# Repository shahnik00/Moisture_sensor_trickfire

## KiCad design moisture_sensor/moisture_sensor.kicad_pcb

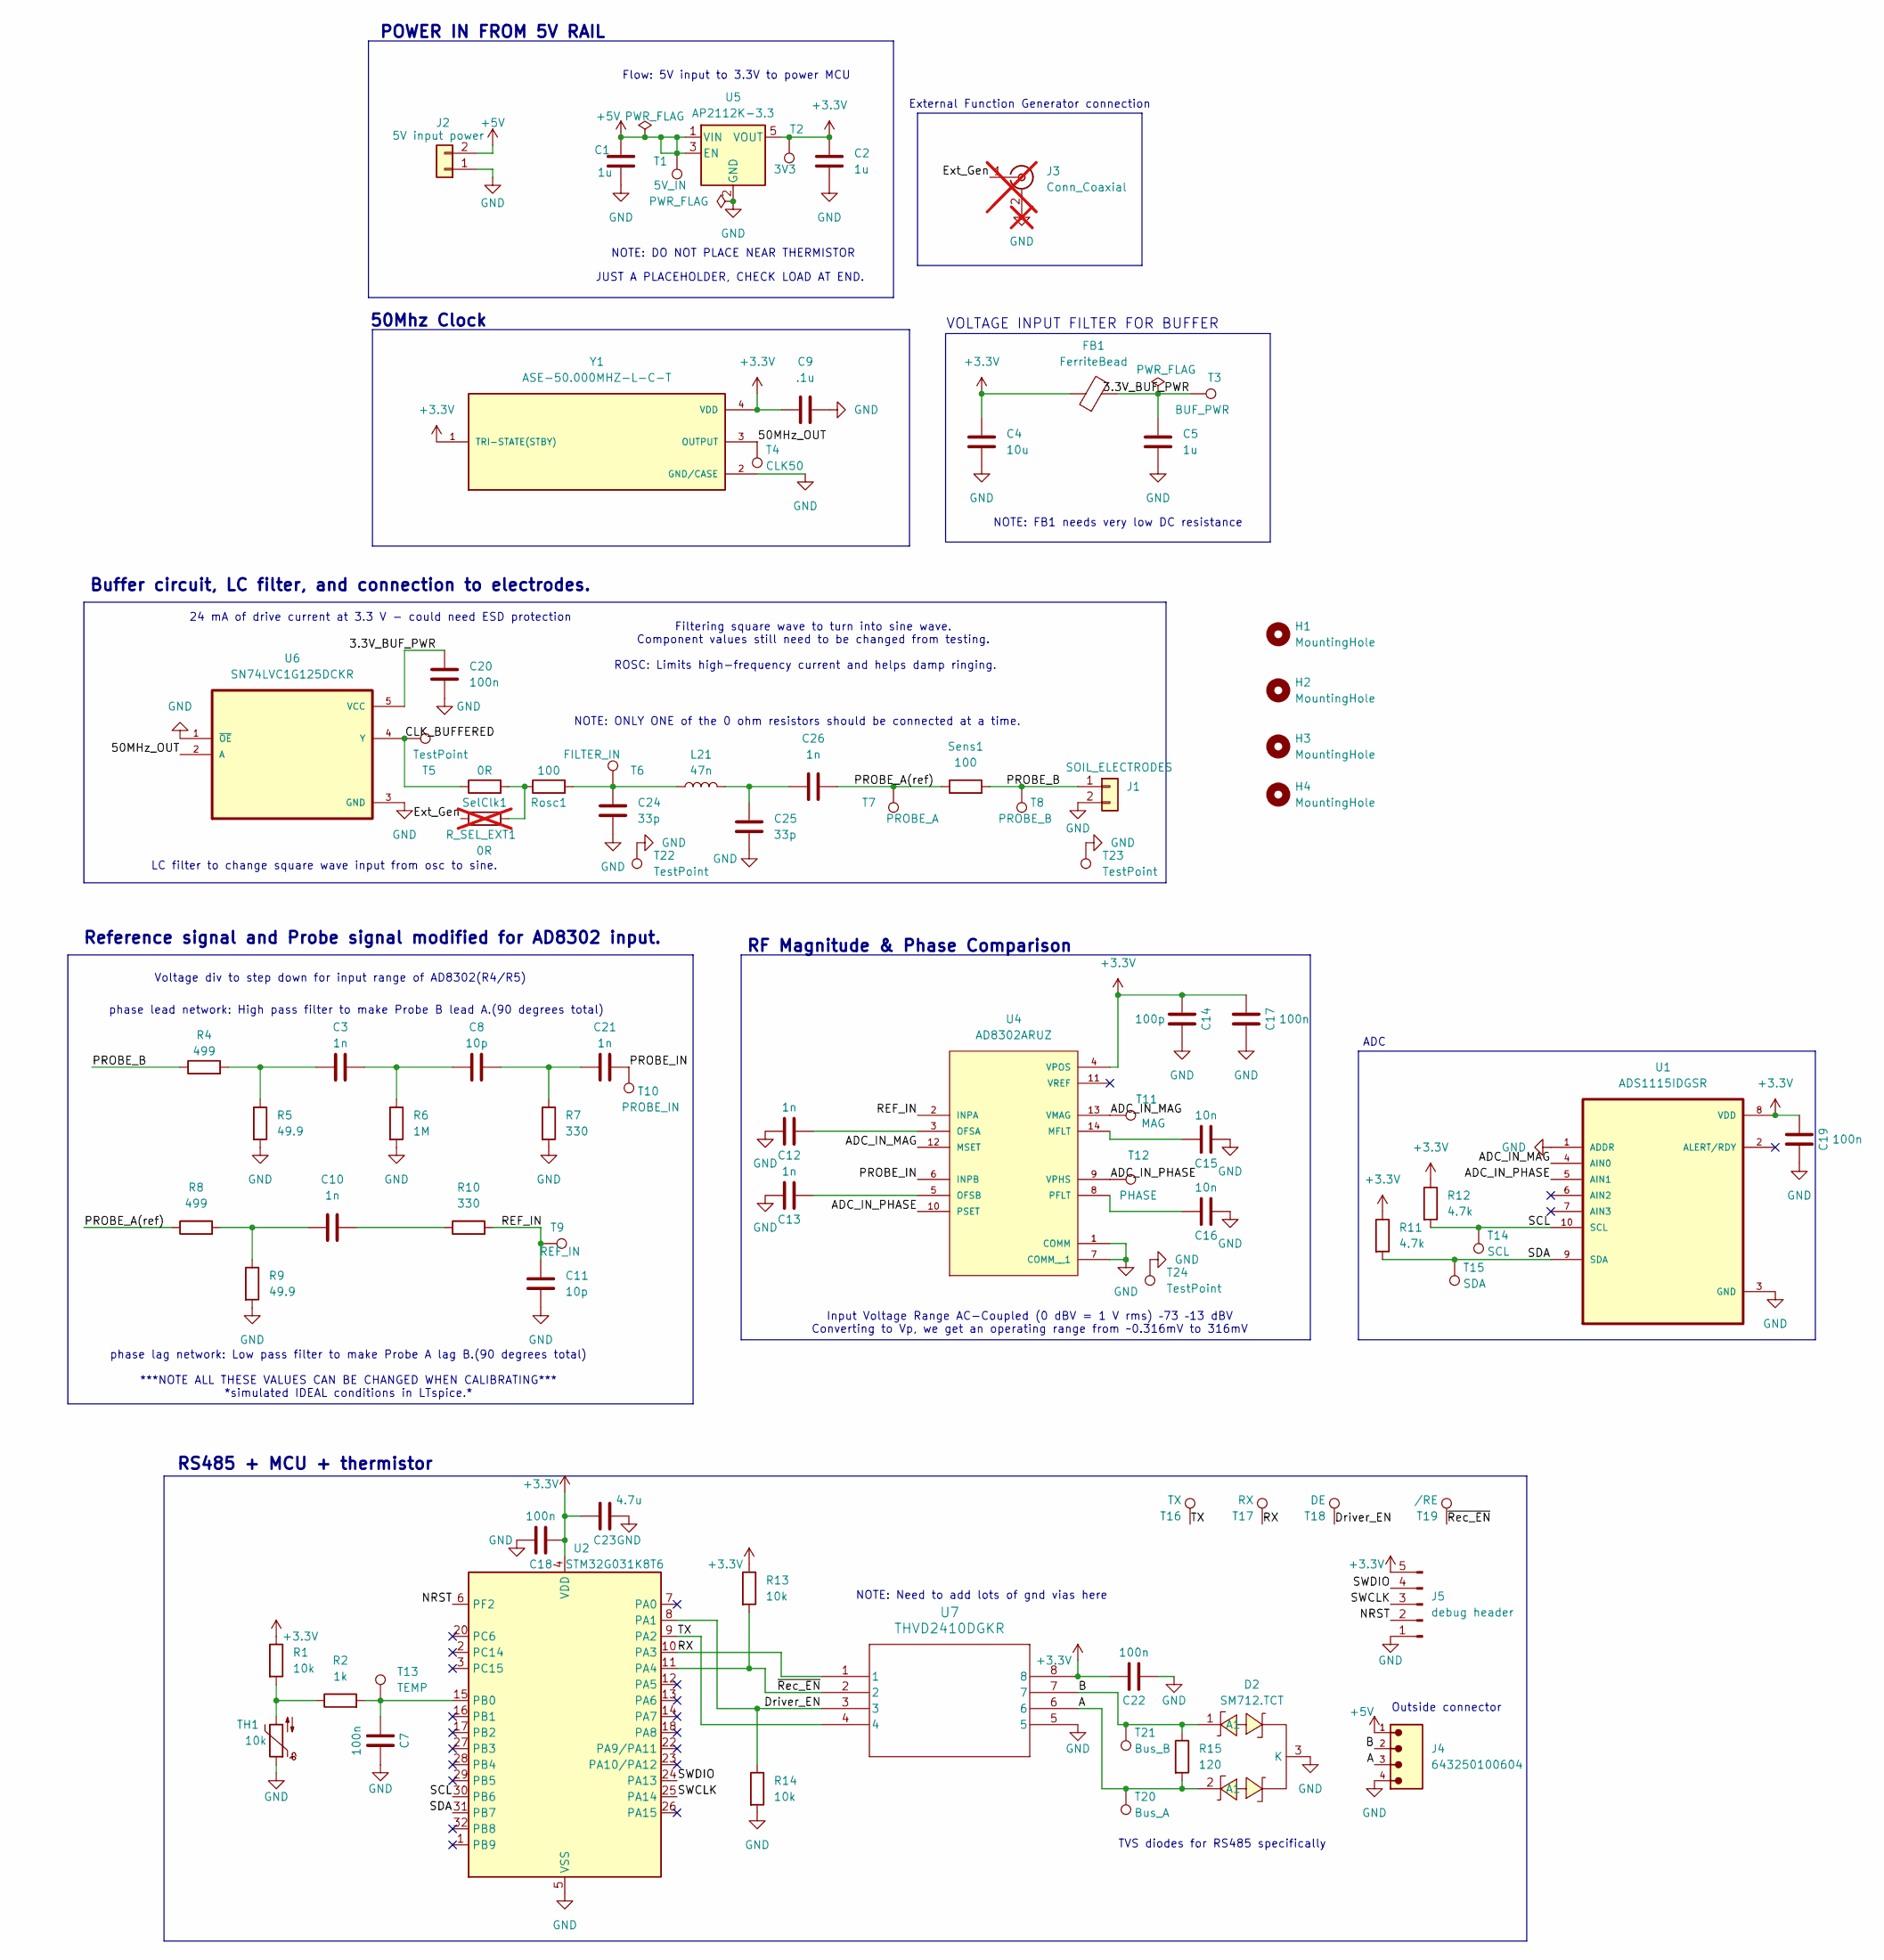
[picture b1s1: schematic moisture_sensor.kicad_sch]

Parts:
C1, C2, C5: 1u; C_0805_2012Metric_Pad1.18x1.45mm_HandSolder
C3, C10, C12, C13, C21, C26: 1n; C_0805_2012Metric_Pad1.18x1.45mm_HandSolder
C4: 10u; C_1206_3216Metric
C7, C17, C18, C19, C20, C22: 100n; C_0805_2012Metric_Pad1.18x1.45mm_HandSolder
C8, C11: 10p; C_0805_2012Metric_Pad1.18x1.45mm_HandSolder
C9: .1u; C_0805_2012Metric_Pad1.18x1.45mm_HandSolder
C14: 100p; C_0805_2012Metric_Pad1.18x1.45mm_HandSolder
C15, C16: 10n; C_0805_2012Metric_Pad1.18x1.45mm_HandSolder
C23: 4.7u; C_1206_3216Metric
C24, C25: 33p; C_0805_2012Metric_Pad1.18x1.45mm_HandSolder
D2: SM712.TCT; SOT-23-3_L3.0-W1.7-P0.95-LS2.9-BR; MPN SM712.TCT; LCSC Part C12067
FB1: FerriteBead; L_0805_2012Metric
H1, H2, H3, H4: MountingHole; MountingHole_3.2mm_M3
J1: SOIL_ELECTRODES; PhoenixContact_MC_1,5_2-G-3.81_1x02_P3.81mm_Horizontal
J2: 5V input power; PinHeader_1x02_P2.54mm_Vertical
J3: Conn_Coaxial; SMA_Amphenol_132134_Vertical; not fitted
J4: 643250100604; MPN 643250100604
J5: debug header; PinHeader_1x05_P2.54mm_Vertical
L21: 47n; L_0805_2012Metric
R1, R13, R14: 10k; R_0805_2012Metric_Pad1.20x1.40mm_HandSolder
R2: 1k; R_0805_2012Metric_Pad1.20x1.40mm_HandSolder
R4, R8: 499; R_0805_2012Metric
R5, R9: 49.9; R_0805_2012Metric
R6: 1M; R_0805_2012Metric
R7, R10: 330; R_0805_2012Metric
R11, R12: 4.7k; R_0805_2012Metric_Pad1.20x1.40mm_HandSolder
R15: 120; R_1206_3216Metric
R_SEL_EXT1: 0R; R_0805_2012Metric; not fitted
Rosc1: 100; R_1206_3216Metric
SelClk1: 0R; R_0805_2012Metric
Sens1: 100; R_1206_3216Metric
T1: 5V_IN; TestPoint_Pad_D1.0mm
T2: 3V3; TestPoint_Pad_D1.0mm
T3: BUF_PWR; TestPoint_Pad_D1.0mm
T4: CLK50; TestPoint_Pad_D1.0mm
T5, T22, T23, T24: TestPoint; TestPoint_Pad_D1.0mm
T6: FILTER_IN; TestPoint_Pad_D1.0mm
T7: PROBE_A; TestPoint_Pad_D1.0mm
T8: PROBE_B; TestPoint_Pad_D1.0mm
T9: REF_IN; TestPoint_Pad_D1.0mm
T10: PROBE_IN; TestPoint_Pad_D1.0mm
T11: MAG; TestPoint_Pad_D1.0mm
T12: PHASE; TestPoint_Pad_D1.0mm
T13: TEMP; TestPoint_Pad_D1.0mm
T14: SCL; TestPoint_Pad_D1.0mm
T15: SDA; TestPoint_Pad_D1.0mm
T16: TX; TestPoint_Pad_D1.0mm
T17: RX; TestPoint_Pad_D1.0mm
T18: DE; TestPoint_Pad_D1.0mm
T19: /RE; TestPoint_Pad_D1.0mm
T20: Bus_A; TestPoint_Pad_D1.0mm
T21: Bus_B; TestPoint_Pad_D1.0mm
TH1: 10k; PhoenixContact_MC_1,5_2-G-3.81_1x02_P3.81mm_Horizontal
U1: ADS1115IDGSR; DGS0010A_N; MPN ADS1115IDGSR
U2: STM32G031K8T6; LQFP-32_7x7mm_P0.8mm
U4: AD8302ARUZ; RU_14_ADI; MPN AD8302ARUZ
U5: AP2112K-3.3; SOT-23-5
U6: SN74LVC1G125DCKR; SOT65P210X110-5N; MPN SN74LVC1G125DCKR
U7: THVD2410DGKR; SOIC_410DGKR_TEX
Y1: ASE-50.000MHZ-L-C-T; XTAL_ASE-50.000MHZ-L-C-T; MPN ASE-50.000MHZ-L-C-T

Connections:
+3.3V: C2.1, C4.1, C9.2, C14.2, C17.2, C18.1, C19.2, C22.1, C23.2, FB1.1, J5.5, R1.1, R11.1, R12.1, R13.1, T2.1, U1.8 (VDD), U2.4 (VDD), U4.4 (VPOS), U5.5 (VOUT), U7.8, Y1.1 (TRI-STATE(STBY)), Y1.4 (VDD)
+5V: C1.1, J2.2, J4.1, T1.1, U5.1 (VIN), U5.3 (EN)
/3.3V_BUF_PWR: C5.1, C20.2, FB1.2, T3.1, U6.5 (VCC)
/50MHz_OUT: T4.1, U6.2 (A), Y1.3 (OUTPUT)
/A: D2.2 (A1), J4.3, R15.2, T20.1, U7.6
/ADC_IN_MAG: T11.1, U1.4 (AIN0), U4.12 (MSET), U4.13 (VMAG)
/ADC_IN_PHASE: T12.1, U1.5 (AIN1), U4.9 (VPHS), U4.10 (PSET)
/B: D2.1 (A1), J4.2, R15.1, T21.1, U7.7
/CLK_BUFFERED: SelClk1.1, T5.1, U6.4 (Y)
/Driver_EN: R14.1, T18.1, U2.8 (PA1), U7.3
/NRST: J5.2, U2.6 (PF2)
/PROBE_A(ref): C26.1, R8.1, Sens1.1, T7.1
/PROBE_B: J1.1, R4.1, Sens1.2, T8.1
/PROBE_IN: C21.2, T10.1, U4.6 (INPB)
/REF_IN: C11.2, R10.2, T9.1, U4.2 (INPA)
/RX: T17.1, U2.10 (PA3), U7.1
/SCL: R12.2, T14.1, U1.10 (SCL), U2.30 (PB6)
/SDA: R11.2, T15.1, U1.9 (SDA), U2.31 (PB7)
/SWCLK: J5.3, U2.25 (PA14)
/SWDIO: J5.4, U2.24 (PA13)
/TX: T16.1, U2.9 (PA2), U7.4
/~Rec_EN: R13.2, T19.1, U2.11 (PA4), U7.2
GND: C1.2, C2.2, C4.2, C5.2, C7.2, C9.1, C11.1, C12.1, C13.1, C14.1, C15.2, C16.2, C17.1, C18.2, C19.1, C20.1, C22.2, C23.1, C24.1, C25.1, D2.3 (K), J1.2, J2.1, J3.2 (Ext), J4.4, J5.1, R5.2, R6.2, R7.2, R9.2, R14.2, T22.1, T23.1, T24.1, TH1.1, U1.1 (ADDR), U1.3 (GND), U2.5 (VSS), U4.1 (COMM), U4.7 (COMM__1), U5.2 (GND), U6.1 (~OE), U6.3 (GND), U7.5, Y1.2 (GND/CASE)
unnamed: C3.1, R4.2, R5.1
unnamed: C3.2, C8.1, R6.1
unnamed: C10.1, R8.2, R9.1
unnamed: C10.2, R10.1
unnamed: C8.2, C21.1, R7.1
unnamed: C24.2, L21.1, Rosc1.2, T6.1
unnamed: C25.2, C26.2, L21.2
unnamed: J3.1 (In), R_SEL_EXT1.2
unnamed: R1.2, R2.1, TH1.2
unnamed: R_SEL_EXT1.1, Rosc1.1, SelClk1.2
unnamed: C7.1, R2.2, T13.1, U2.15 (PB0)
unnamed: C15.1, U4.14 (MFLT)
unnamed: C12.2, U4.3 (OFSA)
unnamed: C13.2, U4.5 (OFSB)
unnamed: C16.1, U4.8 (PFLT)

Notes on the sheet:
NOTE: DO NOT PLACE NEAR THERMISTOR
phase lag network: Low pass filter to make Probe A lag B.(90 degrees total)
POWER IN FROM 5V RAIL
External Function Generator connection
Reference signal and Probe signal modified for AD8302 input.
50Mhz Clock
phase lead network: High pass filter to make Probe B lead A.(90 degrees total)
ADC
JUST A PLACEHOLDER, CHECK LOAD AT END.
RF Magnitude & Phase Comparison
VOLTAGE INPUT FILTER FOR BUFFER
Filtering square wave to turn into sine wave. Component values still need to be changed from testing.
NOTE: ONLY ONE of the 0 ohm resistors should be connected at a time.
NOTE: Need to add lots of gnd vias here
24 mA of drive current at 3.3 V - could need ESD protection
RS485 + MCU + thermistor
Buffer circuit, LC filter, and connection to electrodes.
Flow: 5V input to 3.3V to power MCU
ROSC: Limits high-frequency current and helps damp ringing.
TVS diodes for RS485 specifically
Outside connector
***NOTE ALL THESE VALUES CAN BE CHANGED WHEN CALIBRATING*** *simulated IDEAL conditions in LTspice.*
Input Voltage Range AC-Coupled (0 dBV = 1 V rms) –73 –13 dBV Converting to Vp, we get an operating range from ~0.316mV to 316mV
NOTE: FB1 needs very low DC resistance
Voltage div to step down for input range of AD8302(R4/R5)
LC filter to change square wave input from osc to sine.

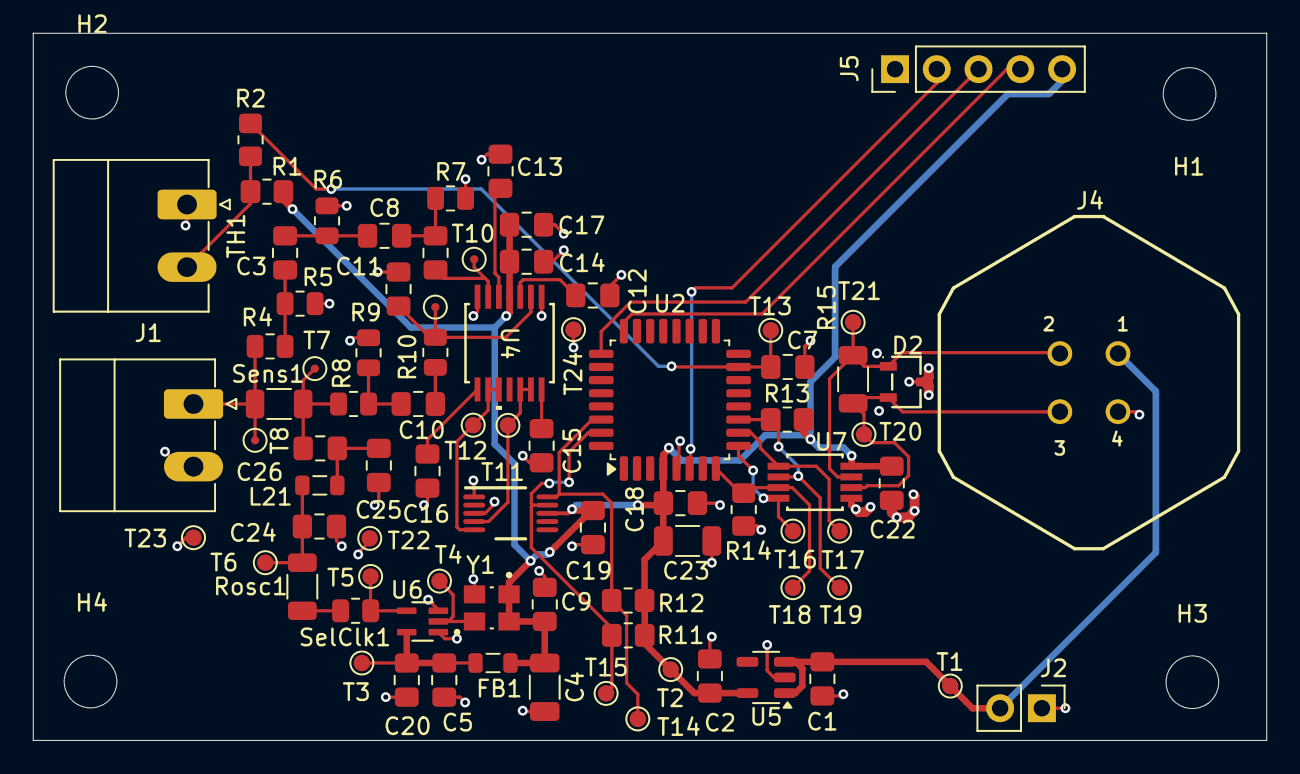
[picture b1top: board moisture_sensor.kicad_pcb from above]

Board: 4 copper layers, 75.0 x 43.0 mm, 85 parts (0 on the bottom side), 37 nets.
